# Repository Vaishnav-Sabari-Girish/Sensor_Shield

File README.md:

# Sensor Shield 

This is my attempt at creating a sensor shield wherein I can connect sensors like MPU9250, MAX30102, DHT22, etc. to one sensor shield that will sit atop a nRF52840DK (Or Arduino Uno) board.

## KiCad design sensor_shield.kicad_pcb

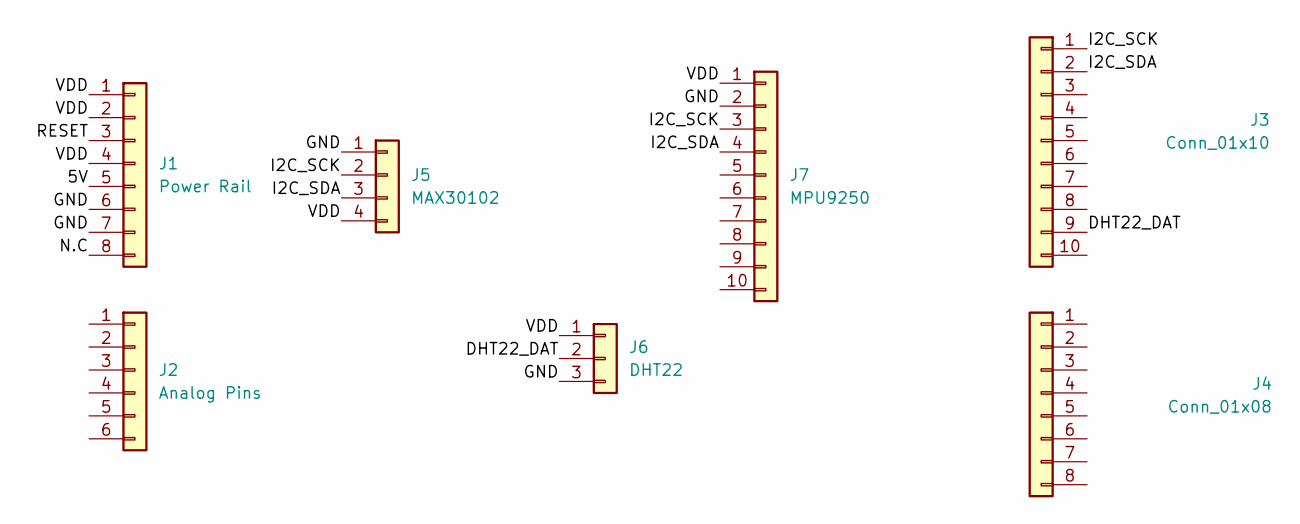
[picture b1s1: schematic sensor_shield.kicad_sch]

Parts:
J1: Power Rail; PinHeader_1x08_P2.54mm_Vertical
J2: Analog Pins; PinHeader_1x06_P2.54mm_Vertical
J3: Conn_01x10; PinHeader_1x10_P2.54mm_Vertical
J4: Conn_01x08; PinHeader_1x08_P2.54mm_Vertical
J5: MAX30102; PinHeader_1x04_P2.54mm_Vertical
J6: DHT22; PinHeader_1x03_P2.54mm_Vertical
J7: MPU9250; PinHeader_1x10_P2.54mm_Vertical

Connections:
/5V: J1.5
/DHT22_DAT: J3.9, J6.2
/GND: J1.6, J1.7, J5.1, J6.3, J7.2
/I2C_SCK: J3.1, J5.2, J7.3
/I2C_SDA: J3.2, J5.3, J7.4
/N.C: J1.8
/RESET: J1.3
/VDD: J1.1, J1.2, J1.4, J5.4, J6.1, J7.1

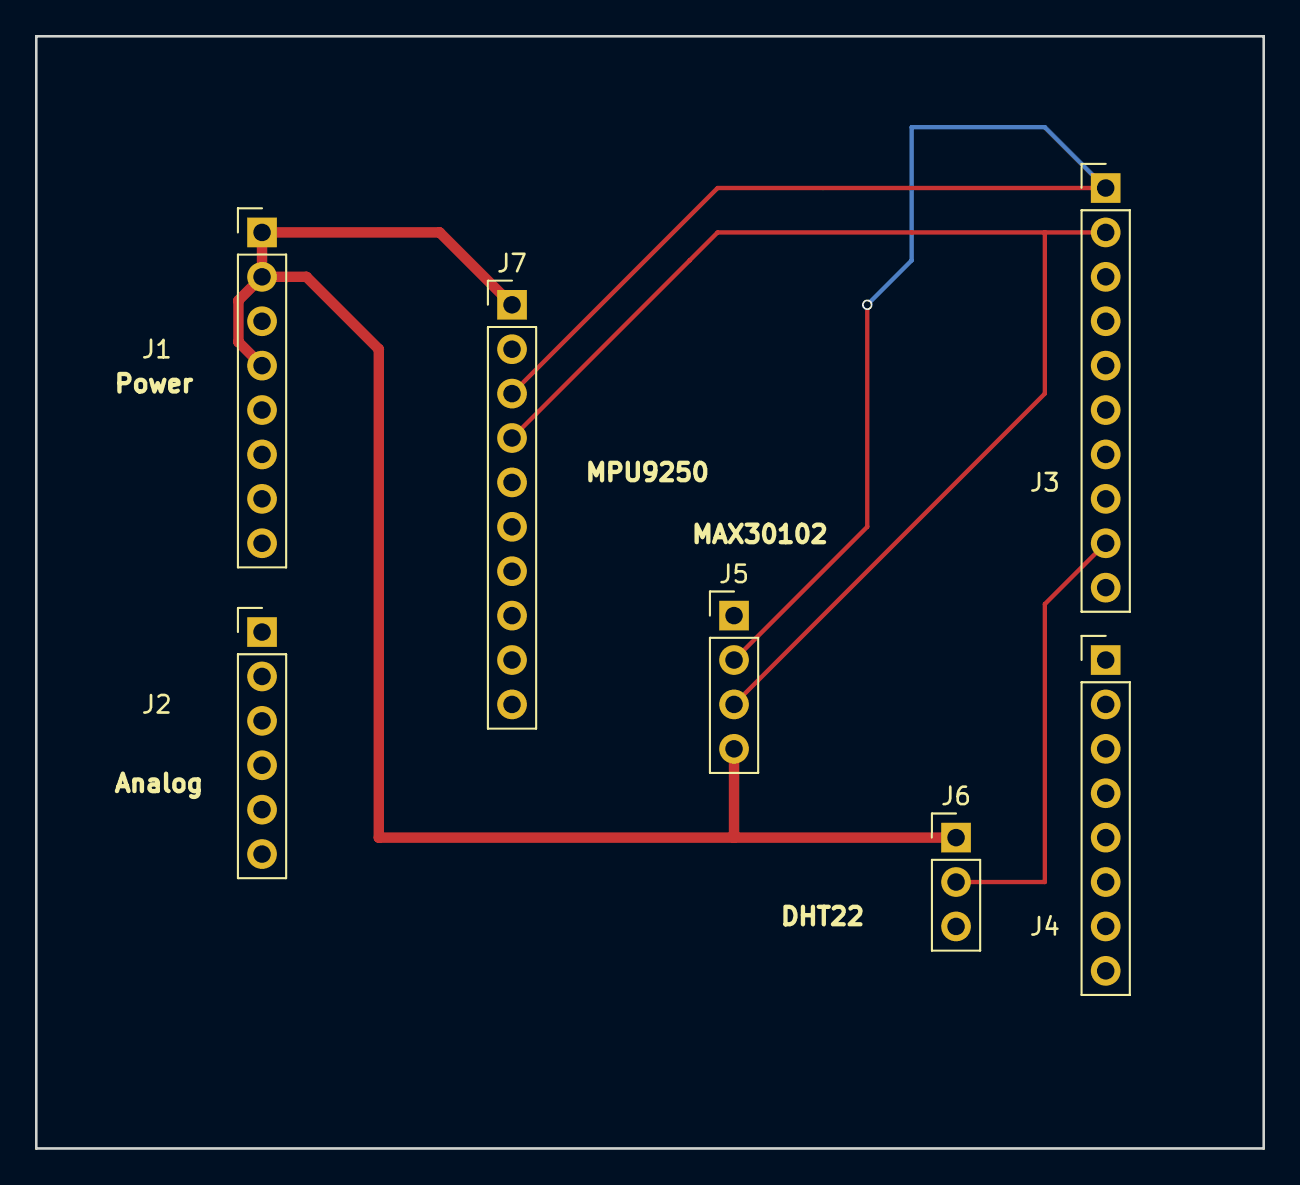
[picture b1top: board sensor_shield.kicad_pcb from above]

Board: 2 copper layers, 70.2 x 63.6 mm, 7 parts (0 on the bottom side), 5 nets.

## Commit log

2026-05-12 feat(initial): Initial commit
2026-05-12 fix(history): History submodule
2026-05-12 feat(basic): Add basic schematic with footprints
2026-05-12 chore(remove history): history removal
2026-05-12 feat(final): Finished
